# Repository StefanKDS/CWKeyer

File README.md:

# CWKeyer

A simple CWKeyer for CW-Paddles based on a ESP8266 with WebInterface.  

SSID:     CWKeyer  
PW:       123456789  
Address:  192.168.4.2  

# Features

- Adjustable speed in WPM and Farnsworth
- Internal buzzer for sound output ( can be deactivated in software )
- LineOut
- 2 Memories for 128 char's each
- WebInterface for setting the memory and training data
- CW Audio decoder ( Under 'Docs' you can find a 'How it works' )

# Images

# PCB

# Circuit

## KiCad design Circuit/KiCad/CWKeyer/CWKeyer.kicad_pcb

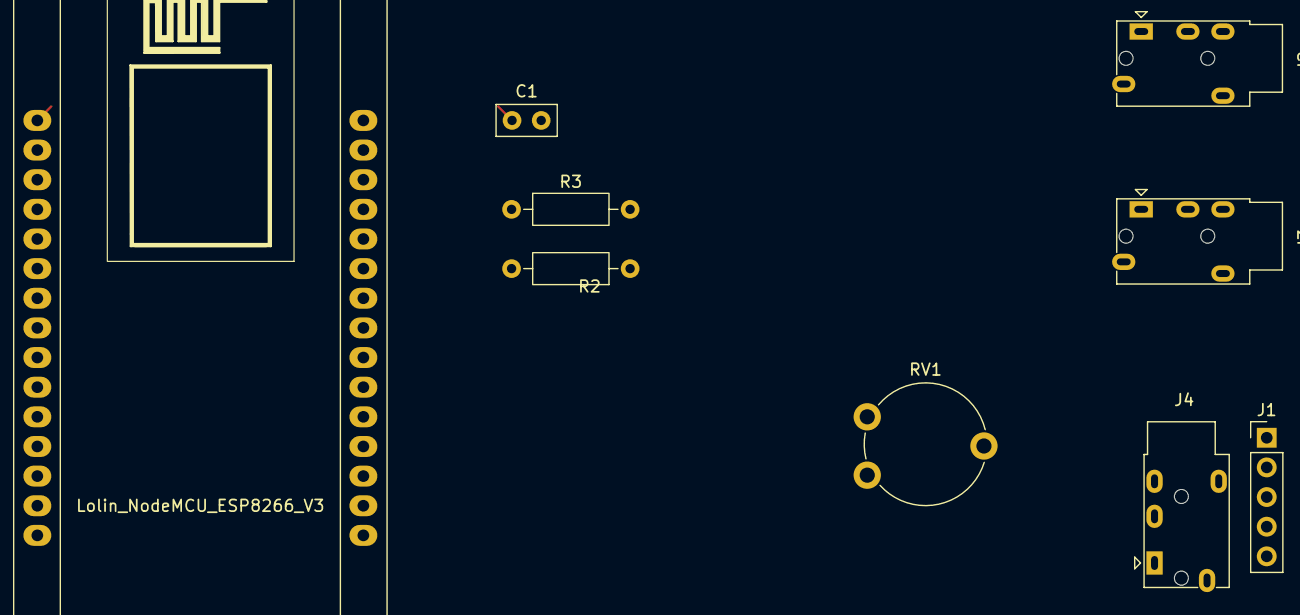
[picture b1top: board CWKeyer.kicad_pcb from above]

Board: 2 copper layers, 9 parts (0 on the bottom side), 12 nets.

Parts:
A1: Lolin_NodeMCU_ESP8266_V3; Lolin_NodeMCU_ESP8266
C1: 100nF_Ceramic; C_Disc_D5.0mm_W2.5mm_P2.50mm
J1: Encoder; PinHeader_1x05_P2.54mm_Vertical
J2: AudioIn; Jack_3.5mm_PJ320E_Horizontal
J3: Headphone; Jack_3.5mm_PJ320E_Horizontal
J4: Keyer; Jack_3.5mm_PJ320E_Horizontal
R2, R3: 10k; R_Axial_DIN0207_L6.3mm_D2.5mm_P10.16mm_Horizontal
RV1: R_Potentiometer; Potentiometer_Piher_PT-10-V10_Vertical

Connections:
unnamed: A1.1 (3V3), R2.1
unnamed: A1.16 (ADC0), C1.1, R2.2, R3.1
unnamed: A1.15 (D0/GPIO16/WAKE), J1.3
unnamed: A1.12 (D3/GPIO0), J1.2
unnamed: A1.11 (D4/GPIO2/TX1), J1.1
unnamed: A1.8 (D5/GPIO14/SCLK), RV1.1
unnamed: A1.7 (D6/GPIO12/MISO), J4.T
unnamed: A1.17 (GND), RV1.3
unnamed: C1.2, J2.T
unnamed: A1.10 (3V3), J1.4
unnamed: A1.29 (GND), J1.5, J2.S, J3.S, J4.S, R3.2
unnamed: J3.T, RV1.2

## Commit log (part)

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2023-11-10 Zwischenübertragung
2023-11-10 Korrektur
2023-11-18 Circuit
2023-11-18 Pictures
2024-01-04 Neue Menüstruktur
2025-02-19 MonitorMode implementiert
2025-08-14 new Page
2025-08-14 Trainer
2025-09-06 Korrekturen ESP8266
2025-09-07 Update Trainer
2025-09-08 Warnings entfernt, Code optimiert
2025-09-08 Strukturierung
2025-09-08 Layout aupdated
2025-09-09 Update Circuit
2025-09-09 Umstellung auf ESP8266WebServer
2025-09-09 Optimierungen
2025-09-09 Übersetzungen
2025-09-09 Non Blocking Beep
2025-09-10 Wifi ON_OFF und Code cleaning
2025-10-08 Update Hear
2025-10-09 Farnsworth
2025-10-09 Schönere Darstellung
2026-01-08 Fix image link in README.md
2026-01-08 Fix image links in README.md
    Updated image links in README to reflect new directory structure.
2026-01-13 Update README with corrected PCB note and image links
2026-03-31 Änderungen
2026-03-31 Iambic B implemetiert
2026-04-06 DisplayFix
2026-04-06 New Trainer Mode
2026-04-12 Optimierung für 20WPM
2026-04-12 Optinierungen
2026-04-12 KiCad circuit
2026-04-12 KiCad
2026-04-12 Kleine Korrekturen
2026-04-12 PCB Update
2026-04-12 Add CW Audio decoder to README
2026-04-12 Add Farnsworth speed adjustment feature to README
2026-04-12 Bilder
2026-04-12 Documentation
2026-04-12 code documentation
